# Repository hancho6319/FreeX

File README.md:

############## Install React-Native ###############

# npx @react-native-community/cli init LEDControlApp

OR

# expo install expo-dev-client
# expo run:android

################# How to Run Your App Now ################
Since you are using Bluetooth, you need to build a development client instead of using Expo Go. Here’s what to do:

1️⃣ Install Expo Dev Client
Run this in your project:

# npm install -g eas-cli

# eas build:configure

2️⃣ Build a Development Client
------------- For Android, run -----------------

# eas build --profile development --platform android

--------------- For iOS (if on macOS)-------------

# eas build --profile development --platform ios

Wait for it to build, then download and install the .apk (Android) or .ipa (iOS) on your device.

3️⃣ Run Your App on a Real Device
Now, use this command to run your app:

------------->  Connect your phone to your PC using a USB cable. <-------------

Open a terminal and run:

# adb devices
# adb pair <DEVICE_IP>:<PAIRING_PORT> <PAIRING_CODE>
# adb connect <DEVICE_IP>:5555

------------------------> All set, then <--------------------------

# npx react-native run-android

# npx expo start --dev-client

############# Alternative: Use an Emulator ############
If you prefer not to build a .apk, you can run the app using Android Studio’s emulator:

# npx expo run:android
Let me know if you need help with this! 🚀

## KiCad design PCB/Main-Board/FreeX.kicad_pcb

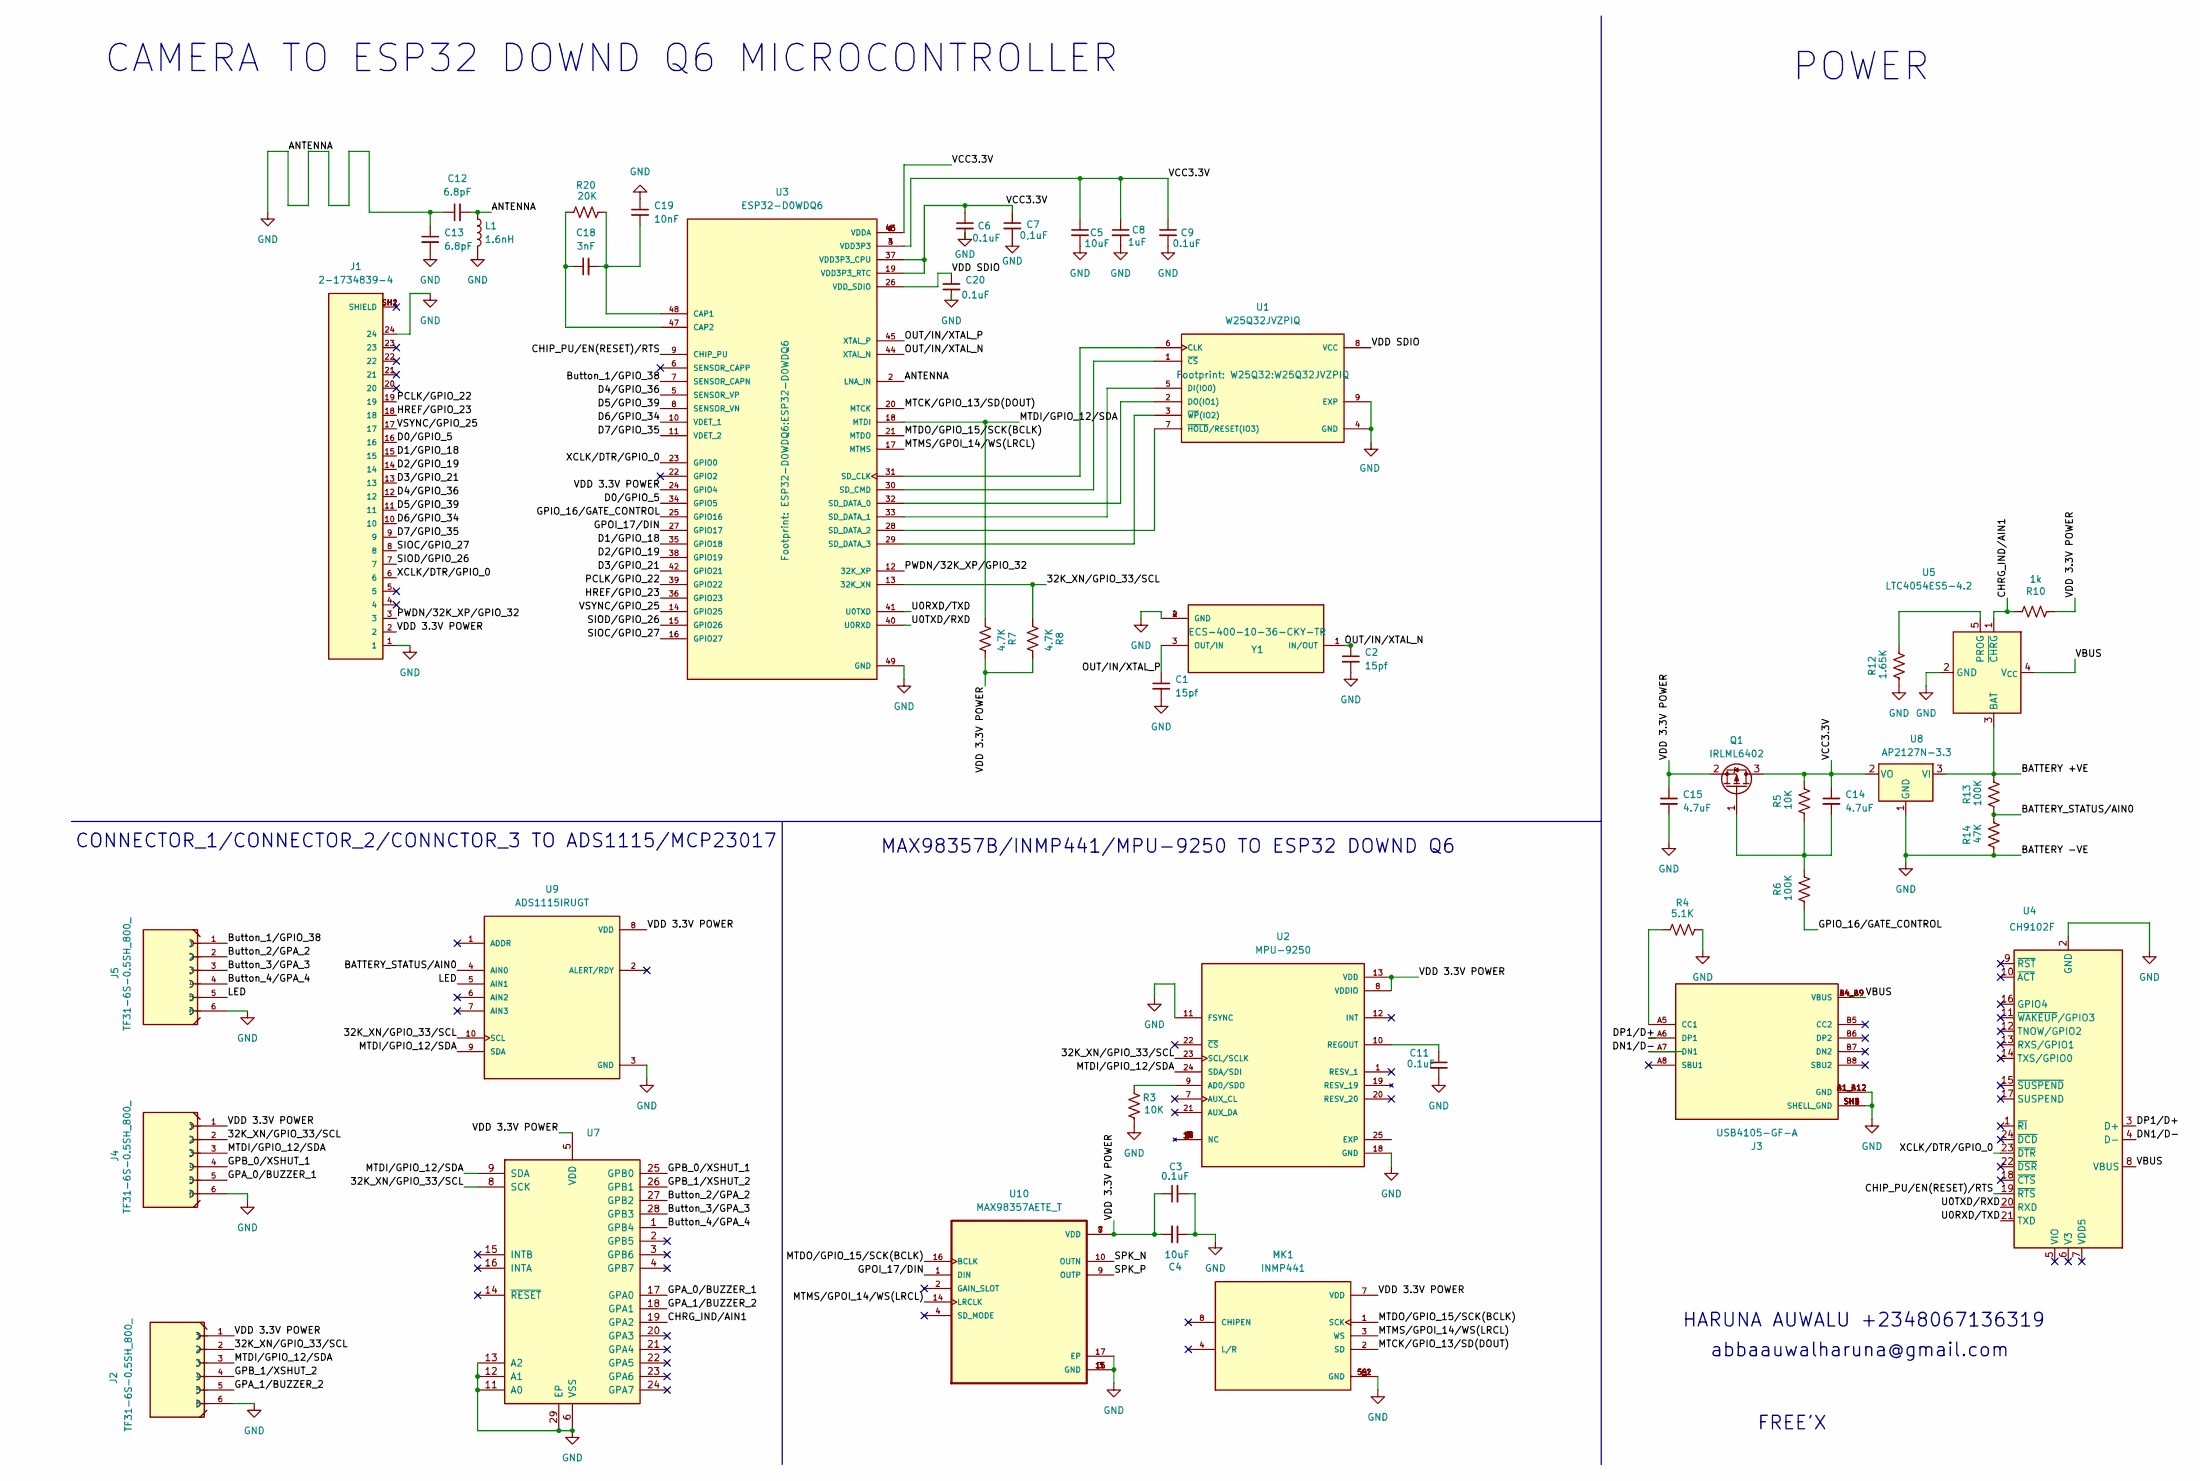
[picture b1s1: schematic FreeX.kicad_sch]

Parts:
C1, C2: 15pf; C_0201_0603Metric
C3, C6, C9, C11, C20: 0.1uF; C_0201_0603Metric
C4, C5: 10uF; C_0201_0603Metric
C7: 0,1uF; C_0201_0603Metric
C8: 1uF; C_0201_0603Metric
C12, C13: 6.8pF; C_0201_0603Metric
C14, C15: 4.7uF; C_0201_0603Metric
C18: 3nF; C_0201_0603Metric
C19: 10nF; C_0201_0603Metric
J1: 2-1734839-4; 2-1734839-4 pin-24; PARTREV 05-06
J2, J4, J5: TF31-6S-0.5SH_800_; TF31-6S-0.5SH_800-6-pins
J3: USB4105-GF-A; USB4105-GF-A TYPE C; PARTREV B4
L1: 1.6nH; L_0201_0603Metric
MK1: INMP441; MIC_INMP441; PARTREV 1.1
Q1: IRLML6402; SOT-23
R3, R5: 10K; R_0201_0603Metric
R4: 5.1K; R_0201_0603Metric
R6, R13: 100K; R_0201_0603Metric
R7, R8: 4.7K; R_0201_0603Metric
R10: 1k; R_0201_0603Metric
R12: 1.65K; R_0201_0603Metric
R14: 47K; R_0201_0603Metric
R20: 20K; R_0201_0603Metric
U1: W25Q32JVZPIQ
U2: MPU-9250; MPU-9250 SENSOR; PARTREV 1.1
U3: ESP32-D0WDQ6; PARTREV v3.9
U4: CH9102F; QFN-24-1EP_4x4mm_P0.5mm_EP2.6x2.6mm
U5: LTC4054ES5-4.2; TSOT-23-5
U7: MCP23017_ML; QFN-28-1EP_6x6mm_P0.65mm_EP4.25x4.25mm
U8: AP2127N-3.3; SOT-23
U9: ADS1115IRUGT; PARTREV B
U10: MAX98357AETE_T
Y1: ECS-400-10-36-CKY-TR; PARTREV 2017

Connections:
/32K_XN/GPIO_33/SCL: J2.2, J4.2, R8.1, U2.23 (SCL/SCLK), U3.13 (32K_XN), U7.8 (SCK), U9.10 (SCL)
/BATTERY +VE: R13.2, U5.3 (BAT), U8.3 (VI)
/BATTERY_STATUS/AIN0: R13.1, R14.2, U9.4 (AIN0)
/Button_1/GPIO_38: J5.1, U3.7 (SENSOR_CAPN)
/Button_2/GPA_2: J5.2, U7.27 (GPB2)
/Button_3/GPA_3: J5.3, U7.28 (GPB3)
/Button_4/GPA_4: J5.4, U7.1 (GPB4)
/CHIP_PU/EN(RESET)/RTS: U3.9 (CHIP_PU), U4.19 (~RTS)
/CHRG_IND/AIN1: R10.1, U5.1 (~CHRG), U7.19 (GPA2)
/D0/GPIO_5: J1.16, U3.34 (GPIO5)
/D1/GPIO_18: J1.15, U3.35 (GPIO18)
/D2/GPIO_19: J1.14, U3.38 (GPIO19)
/D3/GPIO_21: J1.13, U3.42 (GPIO21)
/D4/GPIO_36: J1.12, U3.5 (SENSOR_VP)
/D5/GPIO_39: J1.11, U3.8 (SENSOR_VN)
/D6/GPIO_34: J1.10, U3.10 (VDET_1)
/D7/GPIO_35: J1.9, U3.11 (VDET_2)
/DN1/D-: J3.A7 (DN1), U4.4 (D-)
/DP1/D+: J3.A6 (DP1), U4.3 (D+)
/GPA_0/BUZZER_1: J4.5, U7.17 (GPA0)
/GPA_1/BUZZER_2: J2.5, U7.18 (GPA1)
/GPB_0/XSHUT_1: J4.4, U7.25 (GPB0)
/GPB_1/XSHUT_2: J2.4, U7.26 (GPB1)
/GPIO_16/GATE_CONTROL: R6.1, U3.25 (GPIO16)
/GPOI_17/DIN: U3.27 (GPIO17), U10.1 (DIN)
/HREF/GPIO_23: J1.18, U3.36 (GPIO23)
/LED: J5.5, U9.5 (AIN1)
/MTCK/GPIO_13/SD(DOUT): MK1.2 (SD), U3.20 (MTCK)
/MTDI/GPIO_12/SDA: J2.3, J4.3, R7.1, U2.24 (SDA/SDI), U3.18 (MTDI), U7.9 (SDA), U9.9 (SDA)
/MTDO/GPIO_15/SCK(BCLK): MK1.1 (SCK), U3.21 (MTDO), U10.16 (BCLK)
/MTMS/GPOI_14/WS(LRCL): MK1.3 (WS), U3.17 (MTMS), U10.14 (LRCLK)
/OUT/IN/XTAL_N: C2.1, U3.44 (XTAL_N), Y1.1 (IN/OUT)
/OUT/IN/XTAL_P: C1.1, U3.45 (XTAL_P), Y1.3 (OUT/IN)
/PCLK/GPIO_22: J1.19, U3.39 (GPIO22)
/PWDN/32K_XP/GPIO_32: J1.3, U3.12 (32K_XP)
/SIOC/GPIO_27: J1.8, U3.16 (GPIO27)
/SIOD/GPIO_26: J1.7, U3.15 (GPIO26)
/SPK_N: U10.10 (OUTN)
/SPK_P: U10.9 (OUTP)
/U0RXD/TXD: U3.41 (U0TXD), U4.21 (TXD)
/U0TXD/RXD: U3.40 (U0RXD), U4.20 (RXD)
/VBUS: J3.A4_B9 (VBUS), J3.B4_A9 (VBUS), U4.8 (VBUS), U5.4 (V_{CC})
/VCC3.3V: C5.1, C6.1, C7.1, C8.1, C9.1, C14.1, Q1.3 (D), R5.2, U3.1 (VDDA), U3.3 (VDD3P3), U3.4 (VDD3P3), U3.19 (VDD3P3_RTC), U3.37 (VDD3P3_CPU), U3.43 (VDDA), U3.46 (VDDA), U8.2 (VO)
/VDD 3.3V POWER: C3.1, C4.2, C15.1, J1.2, J2.1, J4.1, MK1.7 (VDD), Q1.2 (S), R7.2, R8.2, R10.2, U2.8 (VDDIO), U2.13 (VDD), U3.24 (GPIO4), U7.5 (VDD), U9.8 (VDD), U10.7 (VDD), U10.8 (VDD)
/VDD SDIO: C20.1, U1.8 (VCC), U3.26 (VDD_SDIO)
/VSYNC/GPIO_25: J1.17, U3.14 (GPIO25)
/XCLK/DTR/GPIO_0: J1.6, U3.23 (GPIO0), U4.23 (~DTR)
GND: C1.2, C2.2, C3.2, C4.1, C5.2, C6.2, C7.2, C8.2, C9.2, C11.2, C12.1, C12.2, C13.1, C13.2, C15.2, C19.1, C20.2, J1.1, J1.24, J2.6, J3.A1_B12 (GND), J3.B1_A12 (GND), J3.SH1 (SHELL_GND), J3.SH2 (SHELL_GND), J3.SH3 (SHELL_GND), J3.SH4 (SHELL_GND), J4.6, J5.6, L1.1, L1.2, MK1.5_1 (GND), MK1.5_2 (GND), MK1.6 (GND), MK1.9 (GND), R3.2, R4.1, R12.1, R14.1, U1.4 (GND), U1.9 (EXP), U2.11 (FSYNC), U2.18 (GND), U3.2 (LNA_IN), U3.49 (GND), U4.2 (GND), U4.25 (GND), U5.2 (GND), U7.6 (VSS), U7.11 (A0), U7.12 (A1), U7.13 (A2), U7.29 (EP), U8.1 (GND), U9.3 (GND), U10.3 (GND), U10.11 (GND), U10.15 (GND), U10.17 (EP), Y1.2 (GND), Y1.4 (GND)
unnamed: J3.A5 (CC1), R4.2
unnamed: C14.2, Q1.1 (G), R5.1, R6.2
unnamed: U1.6 (CLK), U3.31 (SD_CLK)
unnamed: U1.5 (DI(IO0)), U3.33 (SD_DATA_1)
unnamed: U1.2 (DO(IO1)), U3.32 (SD_DATA_0)
unnamed: U1.1 (~CS), U3.30 (SD_CMD)
unnamed: U1.7 (~HOLD/RESET(IO3)), U3.28 (SD_DATA_2)
unnamed: U1.3 (~WP(IO2)), U3.29 (SD_DATA_3)
unnamed: R3.1, U2.9 (AD0/SDO)
unnamed: C11.1, U2.10 (REGOUT)
unnamed: C18.2, C19.2, R20.2, U3.48 (CAP1)
unnamed: C18.1, R20.1, U3.47 (CAP2)
unnamed: R12.2, U5.5 (PROG)

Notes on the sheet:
HARUNA AUWALU +2348067136319
CONNECTOR_1/CONNECTOR_2/CONNCTOR_3 TO ADS1115/MCP23017
MAX98357B/INMP441/MPU-9250 TO ESP32 DOWND Q6
FREE'X
CAMERA TO ESP32 DOWND Q6 MICROCONTROLLER
abbaauwalharuna@gmail.com
POWER

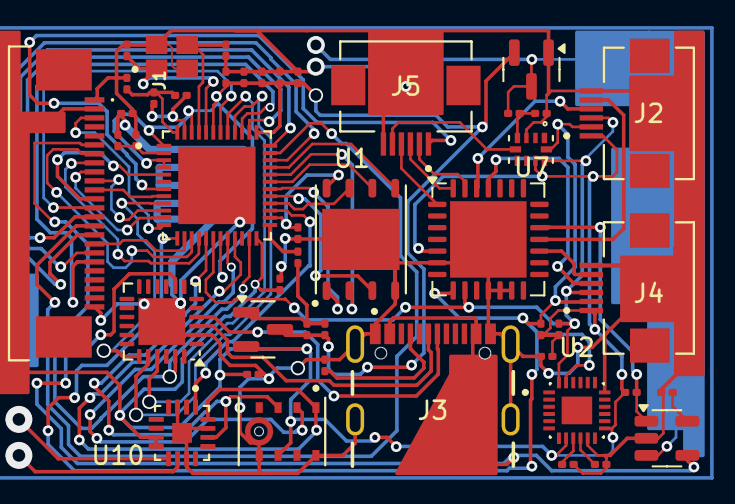
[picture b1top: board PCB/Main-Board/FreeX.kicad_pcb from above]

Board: 2 copper layers, 46 parts (0 on the bottom side), 59 nets.

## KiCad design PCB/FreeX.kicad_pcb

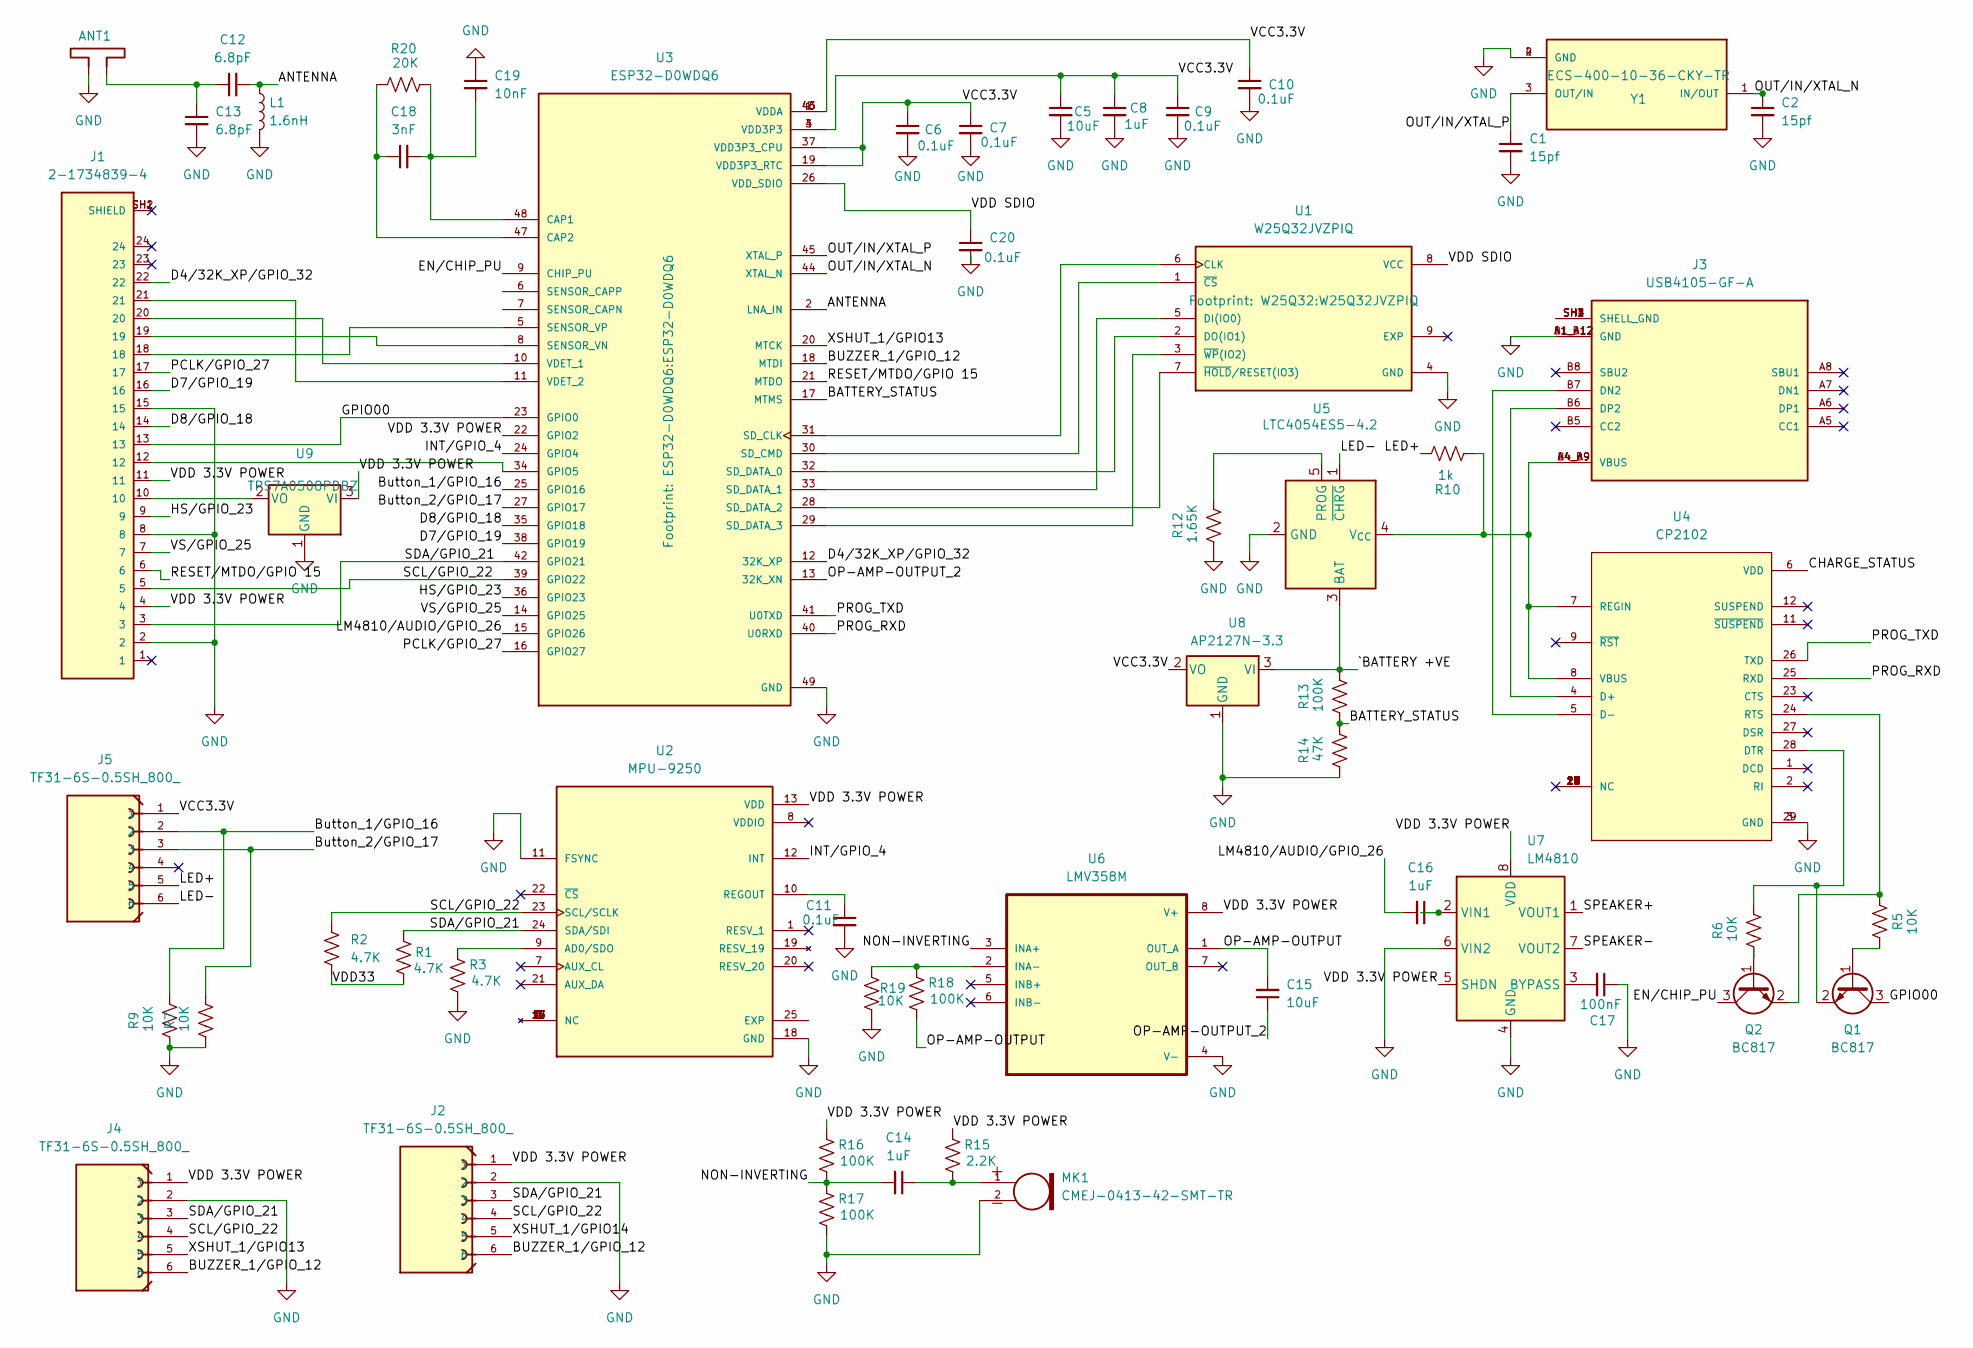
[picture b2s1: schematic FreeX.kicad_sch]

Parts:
ANT1: Antenna_Dipole
C1, C2: 15pf; C_0201_0603Metric
C5, C15: 10uF; C_0201_0603Metric
C6, C9, C10, C11, C20: 0.1uF; C_0201_0603Metric
C7: 0,1uF; C_0201_0603Metric
C8, C14, C16: 1uF; C_0201_0603Metric
C12, C13: 6.8pF; C_0201_0603Metric
C17: 100nF; C_0201_0603Metric
C18: 3nF; C_0201_0603Metric
C19: 10nF; C_0201_0603Metric
J1: 2-1734839-4; 2-1734839-4 pin-24; PARTREV 05-06
J2, J4, J5: TF31-6S-0.5SH_800_; TF31-6S-0.5SH_800-6-pins
J3: USB4105-GF-A; USB4105-GF-A TYPE C; PARTREV B4
L1: 1.6nH; L_0201_0603Metric
MK1: CMEJ-0413-42-SMT-TR; CMEJ-0413-42-SMT-TR-ELECTRET-MIC; PARTREV 1.01
Q1, Q2: BC817; SOT-23
R1, R2, R3: 4.7K; R_0201_0603Metric
R5, R6, R7, R9, R19: 10K; R_0201_0603Metric
R10: 1k; R_0201_0603Metric
R12: 1.65K; R_0201_0603Metric
R13, R16, R17, R18: 100K; R_0201_0603Metric
R14: 47K; R_0201_0603Metric
R15: 2.2K; R_0201_0603Metric
R20: 20K; R_0201_0603Metric
U1: W25Q32JVZPIQ
U2: MPU-9250; MPU-9250 SENSOR; PARTREV 1.1
U3: ESP32-D0WDQ6; PARTREV v3.9
U4: CP2102; CP2102_USB-to-Serial
U5: LTC4054ES5-4.2; TSOT-23-5
U6: LMV358M; LMV358M_OP_AMP_FOR_MIC
U7: LM4810; TSSOP-8_3x3mm_P0.65mm
U8: AP2127N-3.3; SOT-23
U9: TPS7A0508PDBZ; SOT-23
Y1: ECS-400-10-36-CKY-TR; PARTREV 2017

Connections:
/ANTENNA: C12.2, L1.1, U3.2 (LNA_IN)
/BATTERY_STATUS: R13.1, R14.2, U3.17 (MTMS)
/BUZZER_1/GPIO_12: J2.6, J4.6, U3.18 (MTDI)
/Button_1/GPIO_16: J5.2, R9.2, U3.25 (GPIO16)
/Button_2/GPIO_17: J5.3, R7.2, U3.27 (GPIO17)
/CHARGE_STATUS: U4.6 (VDD)
/D4/32K_XP/GPIO_32: J1.22, U3.12 (32K_XP)
/D7/GPIO_19: J1.16, U3.38 (GPIO19)
/D8/GPIO_18: J1.14, U3.35 (GPIO18)
/EN/CHIP_PU: Q2.3 (C), U3.9 (CHIP_PU)
/GPIO00: J1.13, Q1.3 (C), U3.23 (GPIO0)
/HS/GPIO_23: J1.9, U3.36 (GPIO23)
/INT/GPIO_4: U2.12 (INT), U3.24 (GPIO4)
/LED+: J5.5, R10.2
/LED-: J5.6, U5.1 (~CHRG)
/LM4810/AUDIO/GPIO_26: C16.2, U3.15 (GPIO26)
/NON-INVERTING: C14.2, R16.2, R17.1, U6.3 (INA+)
/OP-AMP-OUTPUT: C15.2, R18.2, U6.1 (OUT_A)
/OP-AMP-OUTPUT_2: C15.1, U3.13 (32K_XN)
/OUT/IN/XTAL_N: C2.1, U3.44 (XTAL_N), Y1.1 (IN/OUT)
/OUT/IN/XTAL_P: C1.1, U3.45 (XTAL_P), Y1.3 (OUT/IN)
/PCLK/GPIO_27: J1.17, U3.16 (GPIO27)
/PROG_RXD: U3.40 (U0RXD), U4.25 (RXD)
/PROG_TXD: U3.41 (U0TXD), U4.26 (TXD)
/RESET/MTDO/GPIO 15: J1.6, U3.21 (MTDO)
/SCL/GPIO_22: J1.5, J2.4, J4.4, R2.1, U2.23 (SCL/SCLK), U3.39 (GPIO22)
/SDA/GPIO_21: J1.3, J2.3, J4.3, R1.1, U2.24 (SDA/SDI), U3.42 (GPIO21)
/SPEAKER+: U7.1 (VOUT1)
/SPEAKER-: U7.7 (VOUT2)
/VCC3.3V: C5.1, C6.1, C7.1, C8.1, C9.1, C10.1, J5.1, U3.1 (VDDA), U3.3 (VDD3P3), U3.4 (VDD3P3), U3.19 (VDD3P3_RTC), U3.37 (VDD3P3_CPU), U3.43 (VDDA), U3.46 (VDDA), U8.2 (VO)
/VDD33: R1.2, R2.2
/VDD 3.3V POWER: J1.4, J1.11, J2.1, J4.1, R15.1, R16.1, U2.13 (VDD), U3.22 (GPIO2), U6.8 (V+), U7.5 (SHDN), U7.8 (VDD), U9.3 (VI)
/VDD SDIO: C20.1, U1.8 (VCC), U3.26 (VDD_SDIO)
/VS/GPIO_25: J1.7, U3.14 (GPIO25)
/XSHUT_1/GPIO13: J4.5, U3.20 (MTCK)
/XSHUT_1/GPIO14: J2.5
/`BATTERY +VE: R13.2, U5.3 (BAT), U8.3 (VI)
GND: ANT1.1, C1.2, C2.2, C5.2, C6.2, C7.2, C8.2, C9.2, C10.2, C11.2, C13.2, C17.1, C19.1, C20.2, J1.2, J1.8, J1.15, J2.2, J3.A1_B12 (GND), J3.B1_A12 (GND), J4.2, L1.2, MK1.2, R3.2, R7.1, R9.1, R12.1, R14.1, R17.2, R19.2, U1.4 (GND), U2.11 (FSYNC), U2.18 (GND), U3.49 (GND), U4.3 (GND), U4.29 (GND), U5.2 (GND), U6.4 (V-), U7.4 (GND), U7.6 (VIN2), U8.1 (GND), U9.1 (GND), Y1.2 (GND), Y1.4 (GND)
unnamed: ANT1.2, C12.1, C13.1
unnamed: C14.1, MK1.1, R15.2
unnamed: J3.B7 (DN2), U4.5 (D-)
unnamed: J3.B6 (DP2), U4.4 (D+)
unnamed: J3.SH1 (SHELL_GND), J3.SH2 (SHELL_GND), J3.SH3 (SHELL_GND), J3.SH4 (SHELL_GND)
unnamed: Q1.1 (B), R5.1
unnamed: Q1.2 (E), R6.2, U4.28 (DTR)
unnamed: Q2.1 (B), R6.1
unnamed: Q2.2 (E), R5.2, U4.24 (RTS)
unnamed: U1.6 (CLK), U3.31 (SD_CLK)
unnamed: U1.5 (DI(IO0)), U3.33 (SD_DATA_1)
unnamed: U1.2 (DO(IO1)), U3.32 (SD_DATA_0)
unnamed: U1.1 (~CS), U3.30 (SD_CMD)
unnamed: U1.7 (~HOLD/RESET(IO3)), U3.28 (SD_DATA_2)
unnamed: U1.3 (~WP(IO2)), U3.29 (SD_DATA_3)
unnamed: R3.1, U2.9 (AD0/SDO)
unnamed: C11.1, U2.10 (REGOUT)
unnamed: C18.2, C19.2, R20.2, U3.48 (CAP1)
unnamed: C18.1, R20.1, U3.47 (CAP2)
unnamed: J1.12, U3.34 (GPIO5)
unnamed: J1.19, U3.8 (SENSOR_VN)
unnamed: J1.18, U3.5 (SENSOR_VP)
unnamed: J1.20, U3.10 (VDET_1)
unnamed: J1.21, U3.11 (VDET_2)
unnamed: J3.A4_B9 (VBUS), J3.B4_A9 (VBUS), R10.1, U4.7 (REGIN), U4.8 (VBUS), U5.4 (V_{CC})
unnamed: R12.2, U5.5 (PROG)
unnamed: R18.1, R19.1, U6.2 (INA-)
unnamed: C17.2, U7.3 (BYPASS)
unnamed: C16.1, U7.2 (VIN1)
unnamed: J1.10, U9.2 (VO)

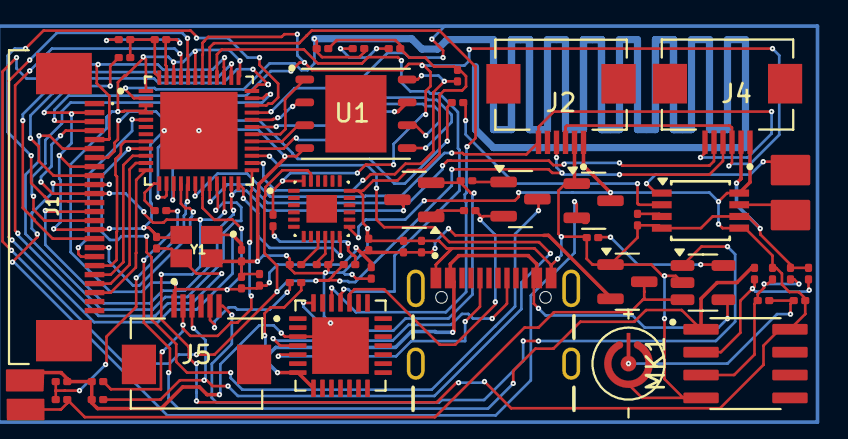
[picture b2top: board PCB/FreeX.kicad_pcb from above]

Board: 2 copper layers, 54 parts (0 on the bottom side), 64 nets.

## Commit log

2025-03-02 2nd Feb 2025
2025-03-03 3rd March 2025
2025-03-04 4th march 2025
2025-03-06 6rd march 2025
2025-03-09 9th, March 2025
2025-03-14 14th, march. 2025
2025-03-15 15th, march. 2025
2025-03-19 19th March 2025
2025-03-26 26th April 2025
2025-03-28 28th,March.2025
2025-04-19 4th, April. 2025
